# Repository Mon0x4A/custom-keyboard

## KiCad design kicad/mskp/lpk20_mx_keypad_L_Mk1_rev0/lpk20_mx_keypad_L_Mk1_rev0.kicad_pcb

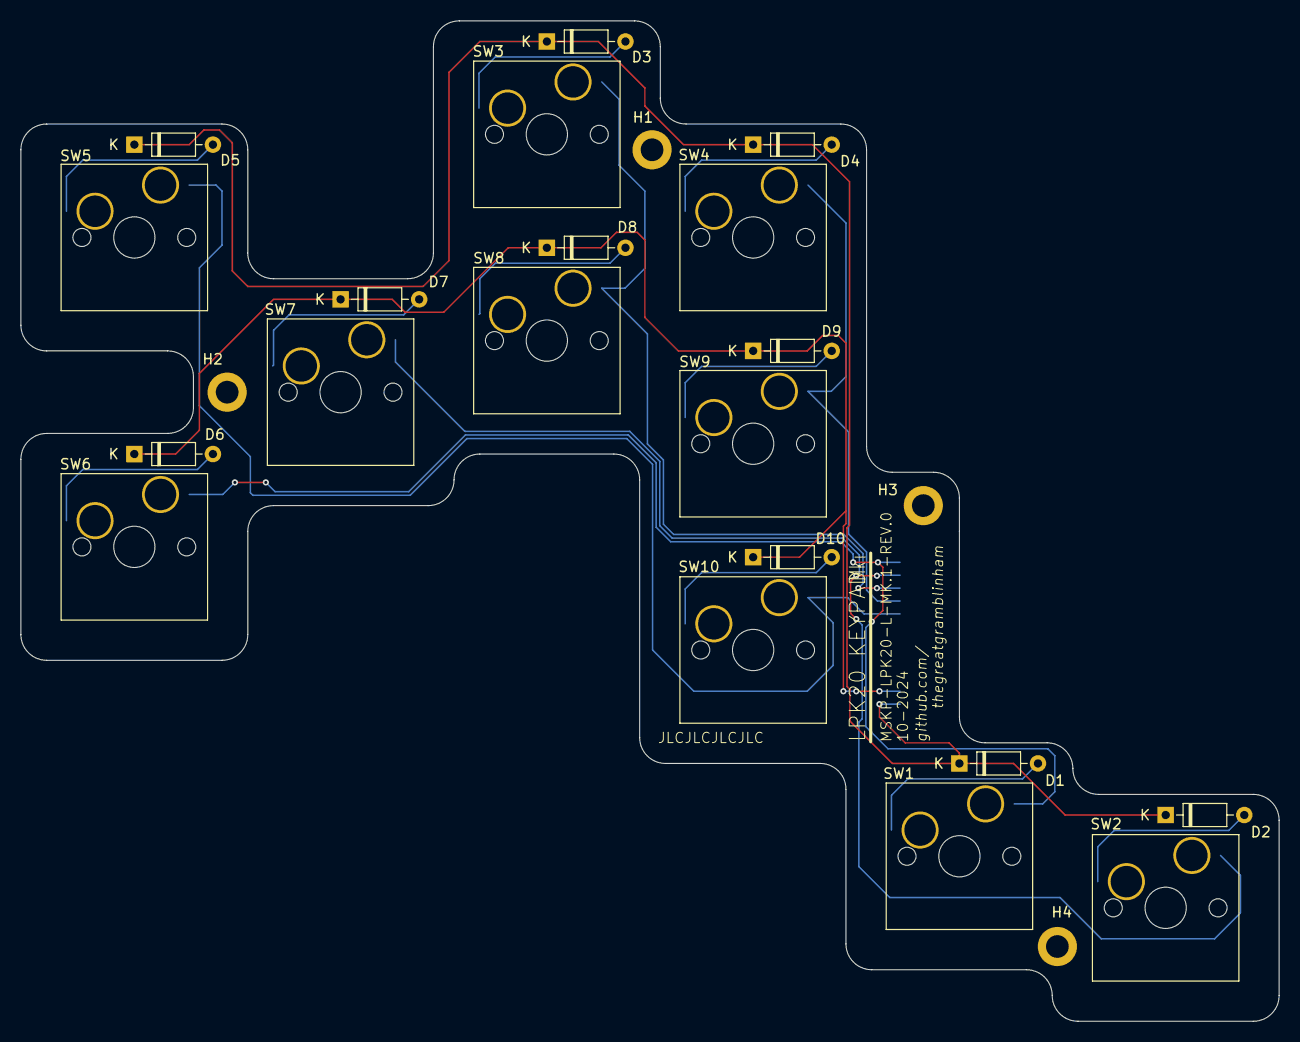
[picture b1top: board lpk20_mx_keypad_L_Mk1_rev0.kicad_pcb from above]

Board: 2 copper layers, 122.0 x 97.0 mm, 25 parts (1 on the bottom side), 17 nets.

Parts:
D1, D2, D3, D4, D5, D6, D7, D8, D9, D10: 1N4148; D_DO-35_SOD27_P7.62mm_Horizontal
H1, H2, H3, H4: MountingHole_2.2mm_M2_ISO14580_Pad
J1: Conn_01x12_Socket; JST_GH_BM12B-GHS-TBT_1x12-1MP_P1.25mm_Vertical
SW1, SW2, SW3, SW4, SW5, SW6, SW7, SW8, SW9, SW10: Switch; Hotswap_MX_Plated_1.00u

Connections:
unnamed: D1.2 (A), SW1.1
unnamed: D1.1 (K), D2.1 (K), D3.1 (K), D4.1 (K), D5.1 (K), J1.1
unnamed: D2.2 (A), SW2.1
unnamed: D3.2 (A), SW3.1
unnamed: D4.2 (A), SW4.1
unnamed: D5.2 (A), SW5.1
unnamed: D6.2 (A), SW6.1
unnamed: D7.2 (A), SW7.1
unnamed: D8.2 (A), SW8.1
unnamed: D9.2 (A), SW9.1
unnamed: D10.2 (A), SW10.1
unnamed: D6.1 (K), D7.1 (K), D8.1 (K), D9.1 (K), D10.1 (K), J1.2
unnamed: J1.8, SW5.2, SW10.2
unnamed: J1.9, SW4.2, SW9.2
unnamed: J1.10, SW3.2, SW8.2
unnamed: J1.11, SW2.2, SW7.2
unnamed: J1.12, SW1.2, SW6.2

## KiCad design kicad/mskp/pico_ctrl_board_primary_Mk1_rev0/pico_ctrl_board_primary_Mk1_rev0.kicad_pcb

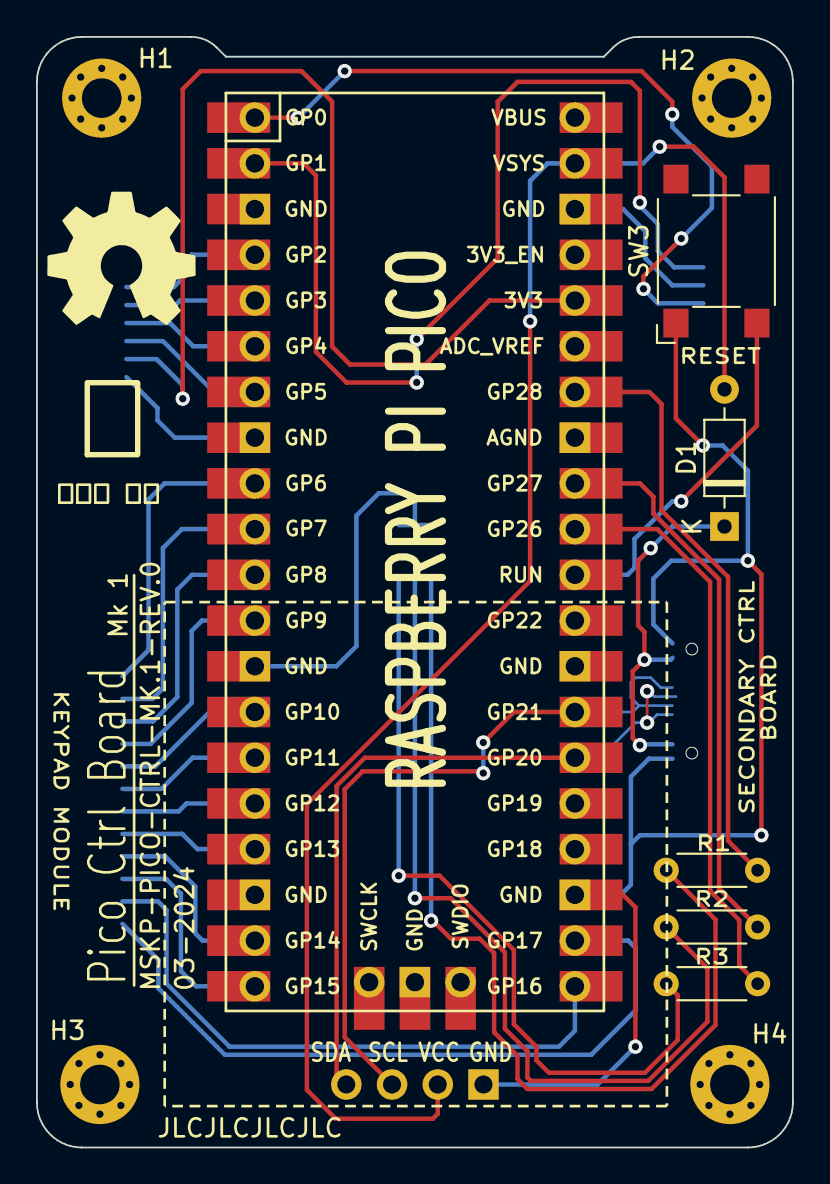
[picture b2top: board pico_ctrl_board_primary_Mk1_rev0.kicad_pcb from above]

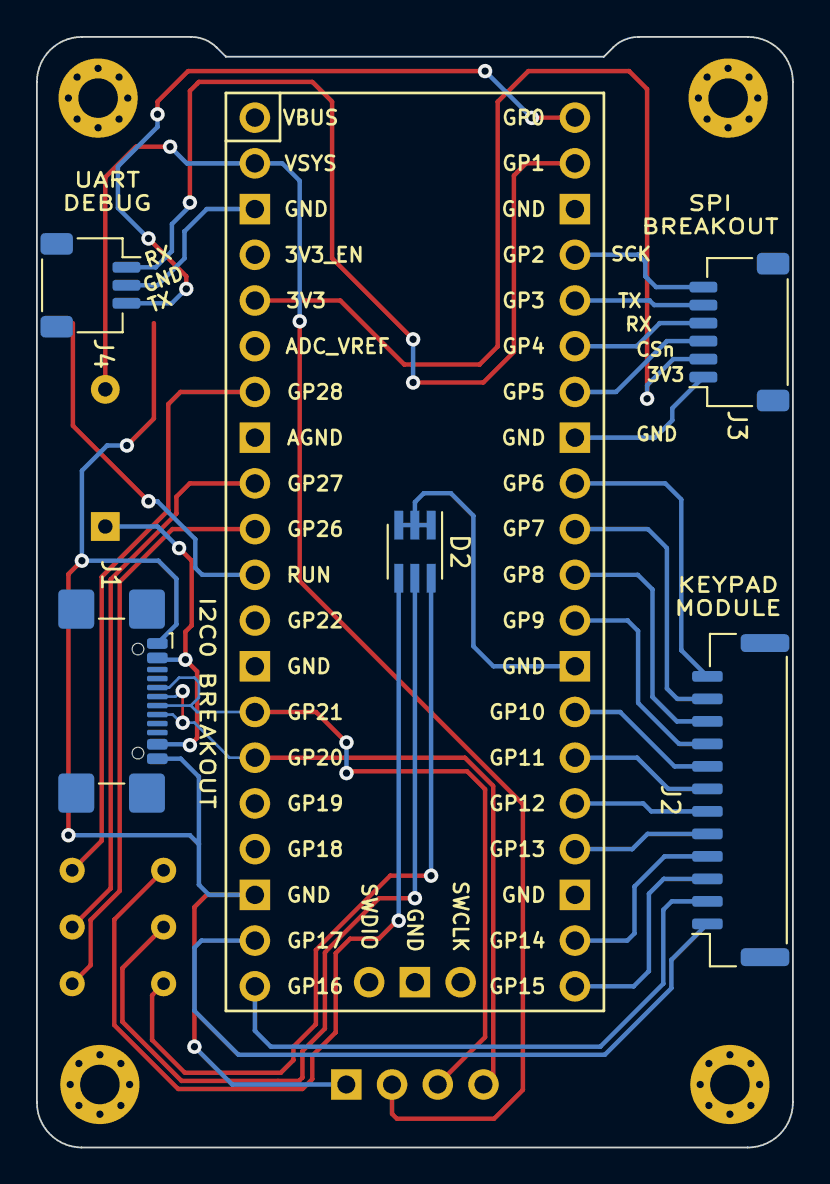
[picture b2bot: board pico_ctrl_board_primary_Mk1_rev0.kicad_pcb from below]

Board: 2 copper layers, 42.0 x 61.7 mm, 16 parts (5 on the bottom side), 34 nets.

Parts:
D1: 1N4148; D_DO-35_SOD27_P7.62mm_Horizontal
D2: ASMT-YTB7-0AA02; LED_Avago_PLCC6_3x2.8mm
H1, H2, H3, H4: MountingHole_2.2mm_M2_Pad_Via
J1: USB_C_Receptacle_USB2.0; USB_C_Receptacle_GCT_USB4110
J2: Conn_01x12_Socket; JST_GH_SM12B-GHS-TB_1x12-1MP_P1.25mm_Horizontal
J3: Conn_01x06_Socket; JST_SH_SM06B-SRSS-TB_1x06-1MP_P1.00mm_Horizontal
J4: Conn_01x03_Socket; JST_SH_SM03B-SRSS-TB_1x03-1MP_P1.00mm_Horizontal
R1, R2, R3: Resistor; R_Axial_DIN0204_L3.6mm_D1.6mm_P5.08mm_Horizontal
SW3: SW_Omron_B3FS; SW_SPST_Omron_B3FS-101xP
U1: Raspberry_Pi_Pico
U2: OLED_128x64

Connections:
GND: J4.2, U1.38 (GND)
unnamed: D1.2 (A), U1.39 (VSYS), U2.2 (VCC)
unnamed: D1.1 (K), J1.A4 (VBUS), J1.A9 (VBUS), J1.B4 (VBUS), J1.B9 (VBUS)
unnamed: D2.6 (AB), R3.1
unnamed: D2.5 (AG), R2.1
unnamed: D2.4 (AR), R1.1
unnamed: D2.1 (KB), D2.2 (KG), D2.3 (KR), U1.13 (GND)
unnamed: J2.1, U1.22 (GPIO17)
unnamed: J2.2, U1.21 (GPIO16)
unnamed: J2.3, U1.20 (GPIO15)
unnamed: J2.4, U1.19 (GPIO14)
unnamed: J2.5, U1.17 (GPIO13)
unnamed: J2.6, U1.16 (GPIO12)
unnamed: J2.7, U1.15 (GPIO11)
unnamed: J2.8, U1.14 (GPIO10)
unnamed: J2.9, U1.12 (GPIO9)
unnamed: J2.10, U1.11 (GPIO8)
unnamed: J2.11, U1.10 (GPIO7)
unnamed: J2.12, U1.9 (GPIO6)
unnamed: J3.1, U1.8 (GND)
unnamed: J3.2, U1.36 (3V3)
unnamed: J3.3, U1.7 (GPIO5)
unnamed: J3.4, U1.6 (GPIO4)
unnamed: J3.5, U1.5 (GPIO3)
unnamed: J3.6, U1.4 (GPIO2)
unnamed: J4.1, U1.2 (GPIO1)
unnamed: J4.3, U1.1 (GPIO0)
unnamed: J1.A6 (D+), J1.B6 (D+), U1.26 (GPIO20), U2.4 (SDA)
unnamed: J1.A7 (D-), J1.B7 (D-), U1.27 (GPIO21), U2.3 (SCL)
unnamed: R3.2, U1.31 (GPIO26_ADC0)
unnamed: R2.2, U1.32 (GPIO27_ADC1)
unnamed: R1.2, U1.34 (GPIO28_ADC2)
unnamed: SW3.2, U1.30 (RUN)
unnamed: J1.A1 (GND), J1.A12 (GND), J1.B1 (GND), J1.B12 (GND), SW3.1, U1.23 (GND), U2.1 (GND)
